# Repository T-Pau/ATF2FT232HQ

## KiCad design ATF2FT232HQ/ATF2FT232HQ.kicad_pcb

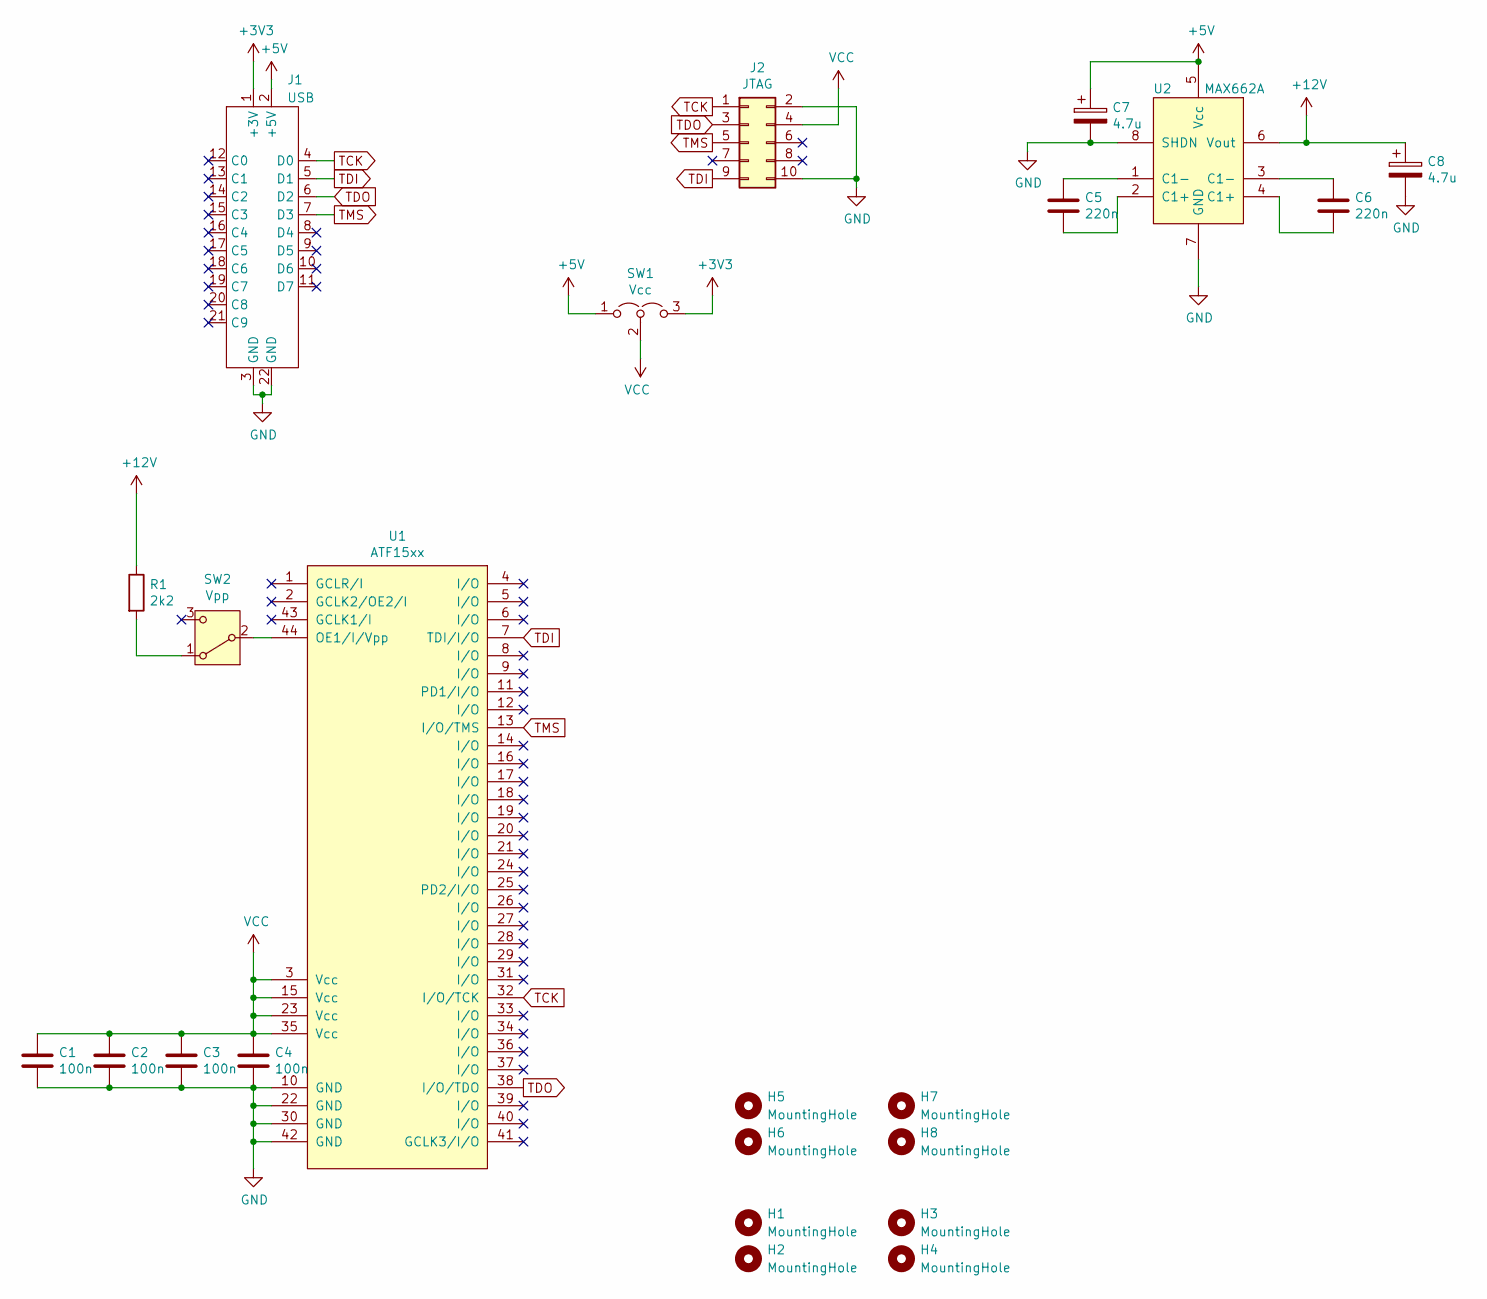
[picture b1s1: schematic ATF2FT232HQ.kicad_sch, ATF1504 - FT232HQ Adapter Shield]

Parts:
C1, C2, C3, C4: 100n; C_Disc_D4.3mm_W1.9mm_P5.00mm
C5, C6: 220n; C_Disc_D4.3mm_W1.9mm_P5.00mm
C7, C8: 4.7u; CP_Radial_D5.0mm_P2.50mm
H1, H2, H3, H4: MountingHole; MountingHole_2.7mm_M2.5
H5, H6, H7, H8: MountingHole; MountingHole_3.2mm_M3
J1: USB; FT232H
J2: JTAG; IDC-Header_2x05_P2.54mm_Vertical
R1: 2k2; R_Axial_DIN0207_L6.3mm_D2.5mm_P10.16mm_Horizontal
SW1: Vcc; SS2513
SW2: Vpp; SS2513
U1: ATF15xx; PLCC-44_THT-Socket
U2: MAX662A; DIP-8_W7.62mm_LongPads

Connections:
+3V3: J1.1 (+3V), SW1.3 (B)
+5V: C7.1, J1.2 (+5V), SW1.1 (A), U2.5 (Vcc)
+12V: C8.1, R1.1, U2.6 (Vout)
GND: C1.2, C2.2, C3.2, C4.2, C7.2, C8.2, J1.3 (GND), J1.22 (GND), J2.2, J2.10, U1.10 (GND), U1.22 (GND), U1.30 (GND), U1.42 (GND), U2.7 (GND), U2.8 (SHDN)
unnamed: C5.1, U2.1 (C1-)
unnamed: C5.2, U2.2 (C1+)
unnamed: C6.1, U2.3 (C1-)
unnamed: C6.2, U2.4 (C1+)
unnamed: R1.2, SW2.1 (A)
unnamed: SW2.2 (B), U1.44 (OE1/I/Vpp)
TCK: J1.4 (D0), J2.1, U1.32 (I/O/TCK)
TDI: J1.5 (D1), J2.9, U1.7 (TDI/I/O)
TDO: J1.6 (D2), J2.3, U1.38 (I/O/TDO)
TMS: J1.7 (D3), J2.5, U1.13 (I/O/TMS)
VCC: C1.1, C2.1, C3.1, C4.1, J2.4, SW1.2 (C), U1.3 (Vcc), U1.15 (Vcc), U1.23 (Vcc), U1.35 (Vcc)

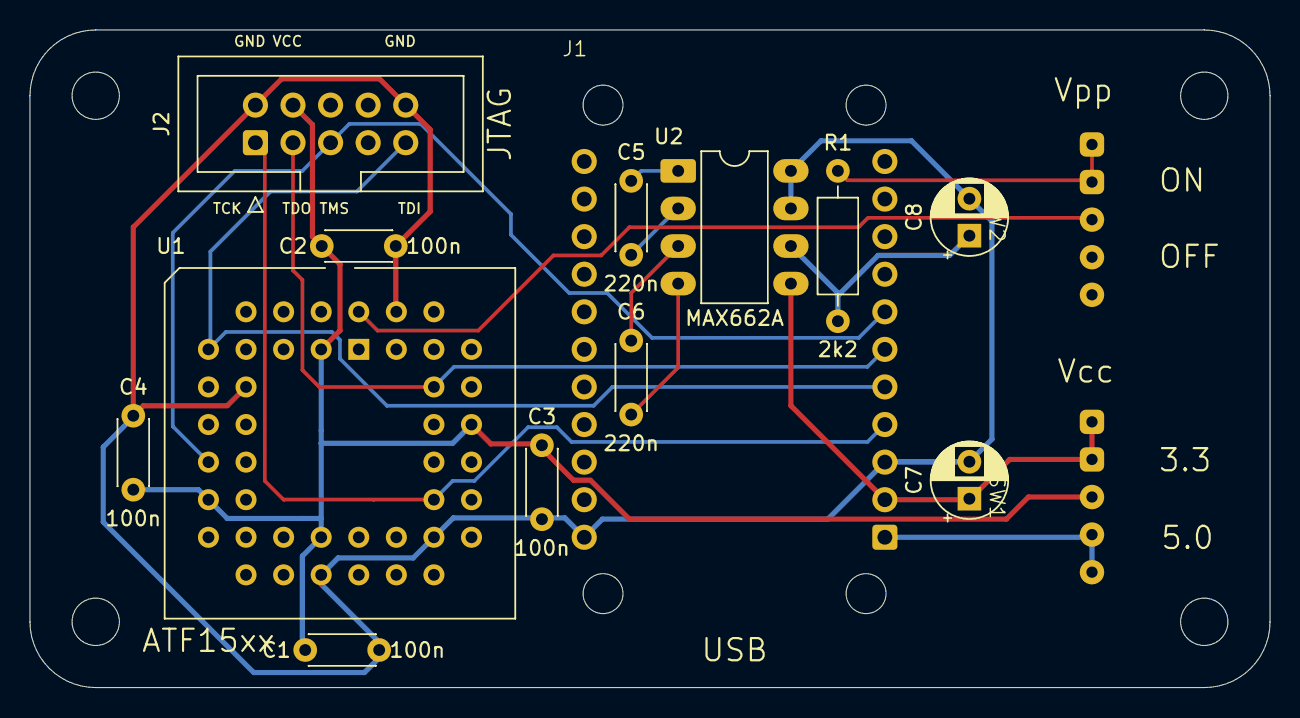
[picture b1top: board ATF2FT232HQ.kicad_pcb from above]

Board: 2 copper layers, 83.8 x 44.4 mm, 23 parts (0 on the bottom side), 15 nets.

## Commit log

2025-05-04 Convert to new FT232H Breakout Board, avoid SMD.
2025-06-11 Fix switch footprint.
